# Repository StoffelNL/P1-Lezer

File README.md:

Een P1-Lezer voor Home Assistant
========

Dit is een simpele P1-lezer voor een 'slimme meter' die integreert met Home Assistant. De lezer is gebaseerd op een WiFi-controller zodat je 'm draadloos kunt verbinden met een home automation-systeem. De enige draad die je nodig hebt is een kabeltje om de lezer op de P1-poort van je slimme meter aan te sluiten.

Onderdelen
----------
Je vindt hier:
- een KiCad-project met een schema, een printplaat en Gerber-bestanden
waarmee je die print kunt laten maken.
- een YAML-bestand voor ESPHome (https://esphome.io/) waarmee je de Wifi-controller kunt programmeren.

### De hardware
Deze P1-lezer is gebaseerd op een ESP8266 WiFi-controller, de WeMos D1 Mini. Dat is een kleine goedkope microcontroller die in dit geval het seriële datasignaal van de slimme meter via een WiFi-verbinding naar je home-automation stuurt.
Je sluit de lezer met een zes-aderige RJ12-kabel aan op de meter.

In de P1-aansluiting worden vijf van de zes pinnen gebruikt (in de volgorde van de RJ12):

1. +5 Volt
2. Data Request
3. Data Ground
4. Not connected
5. Data Transmit
6. Ground

Deze lezer gebruikt ze allemaal. De 5 volt wordt gebruikt als voeding. De Data Request kan je gebruiken om het data-signaal te starten en stoppen (maar het hoeft niet). En de Data Transmit-lijn levert alle meetwaarden. De twee ground-aansluitingen worden aan elkaar gekoppeld.

### De software
Met het YAML-bestand kan je de ESP8266 programmeren. Je kunt dat doen vanuit Home Assistant door de ESPHome-integratie toe te voegen. Een andere methode is de command-line-versie van ESPHome installeren. Dan heb je ook nog Python nodig.

In de YAML-code in deze repo is ook het uitlezen van de gasmeter opgenomen. Heb je geen gekoppelde gasmeter dan kan je dat stukje uit de YAML verwijderen.
Voordat je de D1 Mini gaat progammeren moet je eerst de naam van jouw WiFi-netwerk invullen, met het bijbehorende wachtwoord.

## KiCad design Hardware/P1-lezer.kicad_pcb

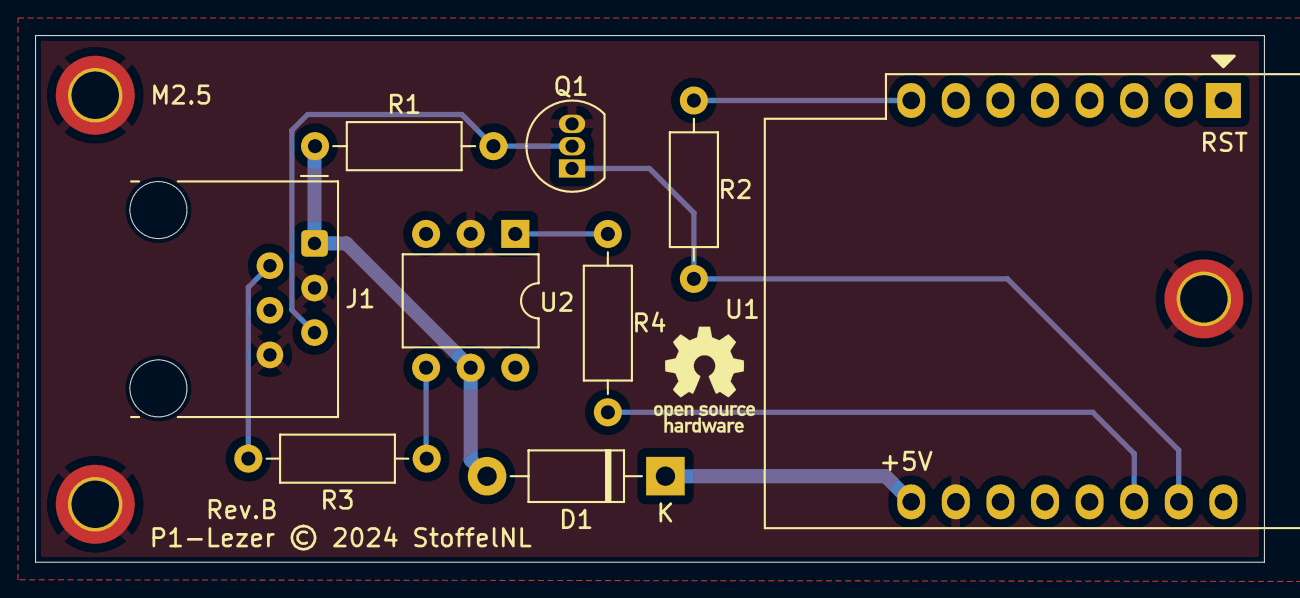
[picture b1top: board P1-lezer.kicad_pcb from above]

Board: 2 copper layers, 70.0 x 30.0 mm, 13 parts (0 on the bottom side), 10 nets.

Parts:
D1: 1N5817; D_DO-41_SOD81_P10.16mm_Horizontal
J1: RJ12; RJ12_Amphenol_54601-x06_Horizontal
M2.5: MountingHole_2.7mm_M2.5_ISO7380_Pad_TopBottom
MH2, MH3: MountingHole_2.7mm_M2.5_ISO7380_Pad_TopBottom
OpenSourceHarware-logo: OSHW-Logo_5.7x6mm_SilkScreen
Q1: BC547; TO-92_Inline
R1: 4k7; R_Axial_DIN0207_L6.3mm_D2.5mm_P10.16mm_Horizontal
R2: 10k; R_Axial_DIN0207_L6.3mm_D2.5mm_P10.16mm_Horizontal
R3: 100; R_Axial_DIN0207_L6.3mm_D2.5mm_P10.16mm_Horizontal
R4: 220; R_Axial_DIN0207_L6.3mm_D2.5mm_P10.16mm_Horizontal
U1: WeMos_D1_mini; WEMOS_D1_mini_light
U2: CNY17-1; DIP-6_W7.62mm

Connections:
+3.3V: R2.1, U1.8 (3V3)
+5V: D1.2 (A), J1.1, R1.1, U2.5
GND: J1.3, J1.6, M2.5.1, MH2.1, MH3.1, Q1.3 (E), U1.10 (GND), U2.2
unnamed: D1.1 (K), U1.9 (5V)
unnamed: J1.2, R3.2
unnamed: J1.5, Q1.2 (B), R1.2
unnamed: Q1.1 (C), R2.2, U1.15 (RX)
unnamed: R3.1, U2.4
unnamed: R4.1, U2.1
Req: R4.2, U1.14 (SCL/D1)

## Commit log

2024-04-23 Revisie toegevoegd op pcb
2024-04-23 NL yaml voor Home Assistent/ESPhome
2024-04-23 License CERN Open Hardware Licence Version 2 - Strongly Reciprocal
2024-04-23 Beginnetje van de README.md
2024-04-23 Typo in README.md
2024-04-23 Gerbers
2024-04-23 *.lck toegevoegd aan .gitignore
2024-04-29 re-routed signal slightly, checked RJ12 dimensions, regenerated gerbers.
2024-04-29 README.md uitgebreid.
2024-04-29 ordered list nu goed.
2024-05-04 Added dimension lines.
2024-05-04 Added github-URL
2024-05-05 Locked mounting holes
2024-05-07 NOTICE added
2024-05-12 Changed board to d1 mini
2024-05-12 Added list with different track widths
2024-05-12 Moved request line from D5 to D4 and added 'request_interval: 0ms' explicitly to config instead of relying on needing to know that 0ms is the default.
2024-05-12 Moved the request output from D4 to D5.
2024-05-12 Waarschuwing erbij gezet.
2024-05-12 Moved request line to D1 and rerouted the board to match this change.
2024-05-12 Changed request line to D1
2024-05-12 Regenerated gerbers
2024-05-12 Waarschuwing weer verwijderd na aanpassingen aan schema, print en yaml.
2024-05-12 Kleine verbeteringen
2024-06-20 Plaatje Prototype.png toegevoegd.
2024-06-20 Plaatje toegevoegd aan README.md
2024-06-20 Tekst onder Software aangepast.
2024-06-20 Optocoupler aangepast naar CNY17-1
2024-07-23 RST en +5V markering toegevoegd aan pcb om orientatie D1 Mini te verduidelijken.

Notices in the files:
Hardware/P1-lezer.kicad_pcb:
P1-Lezer © 2024 StoffelNL
